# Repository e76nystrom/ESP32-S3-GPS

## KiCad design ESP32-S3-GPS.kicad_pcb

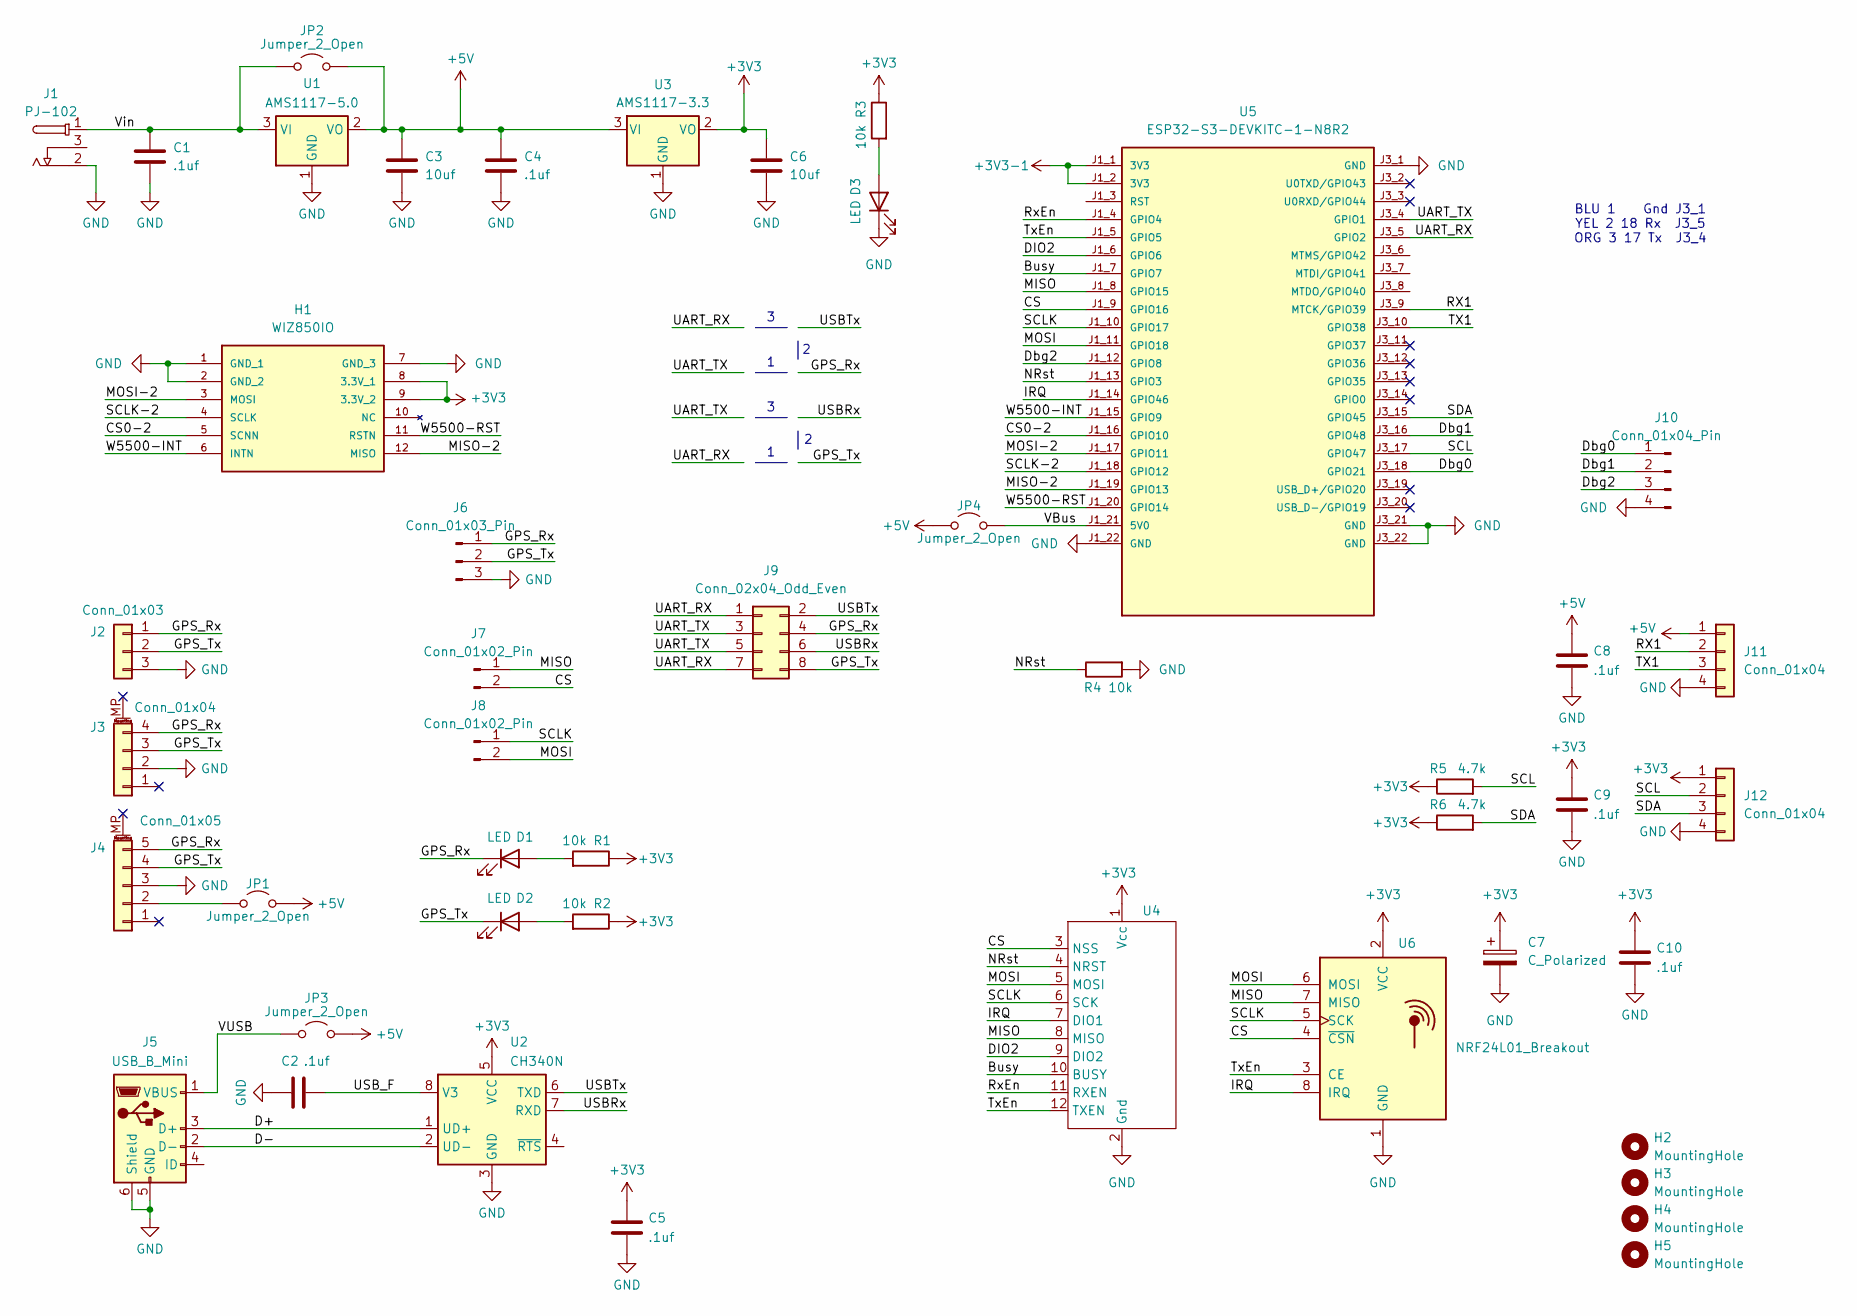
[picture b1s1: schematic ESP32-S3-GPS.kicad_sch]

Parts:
C1, C2, C4, C5, C8, C9, C10: .1uf; C_0805_2012Metric_Pad1.18x1.45mm_HandSolder
C3, C6: 10uf; C_0805_2012Metric_Pad1.18x1.45mm_HandSolder
C7: C_Polarized; CP_EIA-3528-12_Kemet-T_HandSolder
D1, D2, D3: LED; LED_0603_1608Metric_Pad1.05x1.35mm_HandSolder
H1: WIZ850IO; MANUFACTURER_PART_NUMBER WIZ850IO
H2, H3, H4, H5: MountingHole; MountingHole_1-8_1-4
J1: PJ-102; PJ-102-3.81mm
J2: Conn_01x03; JST_XH_B3B-XH-A_1x03_P2.50mm_Vertical
J3: Conn_01x04; JST_GH_SM04B-GHS-TB_1x04-1MP_P1.25mm_Horizontal
J4: Conn_01x05; JST_GH_SM05B-GHS-TB_1x05-1MP_P1.25mm_Horizontal
J5: USB_B_Mini; USB_Mini_B
J6: Conn_01x03_Pin; PinHeader_1x03_P2.54mm_Vertical
J7, J8: Conn_01x02_Pin; PinHeader_1x02_P2.54mm_Vertical
J9: Conn_02x04_Odd_Even; PinHeader_2x04_P2.54mm_Vertical
J10: Conn_01x04_Pin; PinHeader_1x04_P2.54mm_Vertical
J11, J12: Conn_01x04; JST_XH_B4B-XH-A_1x04_P2.50mm_Vertical
JP1, JP3, JP4: Jumper_2_Open; R_0805_2012Metric_Pad1.20x1.40mm_HandSolder
JP2: Jumper_2_Open; R_1206_3216Metric_Pad1.30x1.75mm_HandSolder
R1, R2, R3, R4: 10k; R_0805_2012Metric_Pad1.20x1.40mm_HandSolder
R5, R6: 4.7k; R_0805_2012Metric_Pad1.20x1.40mm_HandSolder
U1: AMS1117-5.0; SOT-223-3_TabPin2
U2: CH340N; JEITA_SOIC-8_3.9x4.9mm_P1.27mm
U3: AMS1117-3.3; SOT-223-3_TabPin2
U4: PinSocket_2x06_P2.54mm_Vertical
U5: ESP32-S3-DEVKITC-1-N8R2; ESP32-S3; PARTREV V1
U6: NRF24L01_Breakout; nRF24L01_Breakout

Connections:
+3V3: C5.1, C6.1, C7.1, C9.1, C10.1, H1.8 (3.3V_1), H1.9 (3.3V_2), J12.1, R1.1, R2.1, R3.1, R5.1, R6.1, U2.5 (VCC), U3.2 (VO), U4.1 (Vcc), U6.2 (VCC)
+3V3-1: U5.J1_1 (3V3), U5.J1_2 (3V3)
+5V: C3.1, C4.1, C8.1, J11.1, JP1.1 (A), JP2.2 (B), JP3.2 (B), JP4.2 (B), U1.2 (VO), U3.3 (VI)
/Busy: U4.10 (BUSY), U5.J1_7 (GPIO7)
/CS: J7.2, U4.3 (NSS), U5.J1_9 (GPIO16), U6.4 (~CSN)
/CS0-2: H1.5 (SCNN), U5.J1_16 (GPIO10)
/D+: J5.3 (D+), U2.1 (UD+)
/D-: J5.2 (D-), U2.2 (UD-)
/DIO2: U4.9 (DIO2), U5.J1_6 (GPIO6)
/Dbg0: J10.1, U5.J3_18 (GPIO21)
/Dbg1: J10.2, U5.J3_16 (GPIO48)
/Dbg2: J10.3, U5.J1_12 (GPIO8)
/GPS_Rx: D1.1 (K), J2.1, J3.4, J4.5, J6.1, J9.4
/GPS_Tx: D2.1 (K), J2.2, J3.3, J4.4, J6.2, J9.8
/IRQ: U4.7 (DIO1), U5.J1_14 (GPIO46), U6.8 (IRQ)
/MISO: J7.1, U4.8 (MISO), U5.J1_8 (GPIO15), U6.7 (MISO)
/MISO-2: H1.12 (MISO), U5.J1_19 (GPIO13)
/MOSI: J8.2, U4.5 (MOSI), U5.J1_11 (GPIO18), U6.6 (MOSI)
/MOSI-2: H1.3 (MOSI), U5.J1_17 (GPIO11)
/NRst: R4.1, U4.4 (NRST), U5.J1_13 (GPIO3)
/RX1: J11.2, U5.J3_9 (MTCK/GPIO39)
/RxEn: U4.11 (RXEN), U5.J1_4 (GPIO4)
/SCL: J12.2, R5.2, U5.J3_17 (GPIO47)
/SCLK: J8.1, U4.6 (SCK), U5.J1_10 (GPIO17), U6.5 (SCK)
/SCLK-2: H1.4 (SCLK), U5.J1_18 (GPIO12)
/SDA: J12.3, R6.2, U5.J3_15 (GPIO45)
/TX1: J11.3, U5.J3_10 (GPIO38)
/TxEn: U4.12 (TXEN), U5.J1_5 (GPIO5), U6.3 (CE)
/UART_RX: J9.1, J9.7, U5.J3_5 (GPIO2)
/UART_TX: J9.3, J9.5, U5.J3_4 (GPIO1)
/USBRx: J9.6, U2.7 (RXD)
/USBTx: J9.2, U2.6 (TXD)
/USB_F: C2.1, U2.8 (V3)
/VBus: JP4.1 (A), U5.J1_21 (5V0)
/VUSB: J5.1 (VBUS), JP3.1 (A)
/Vin: C1.1, J1.1, JP2.1 (A), U1.3 (VI)
/W5500-INT: H1.6 (INTN), U5.J1_15 (GPIO9)
/W5500-RST: H1.11 (RSTN), U5.J1_20 (GPIO14)
GND: C1.2, C2.2, C3.2, C4.2, C5.2, C6.2, C7.2, C8.2, C9.2, C10.2, D3.1 (K), H1.1 (GND_1), H1.2 (GND_2), H1.7 (GND_3), J1.2, J2.3, J3.2, J4.3, J5.5 (GND), J5.6 (Shield), J6.3, J10.4, J11.4, J12.4, R4.2, U1.1 (GND), U2.3 (GND), U3.1 (GND), U4.2 (Gnd), U5.J1_22 (GND), U5.J3_1 (GND), U5.J3_21 (GND), U5.J3_22 (GND), U6.1 (GND)
unnamed: D1.2 (A), R1.2
unnamed: D2.2 (A), R2.2
unnamed: D3.2 (A), R3.2
unnamed: J4.2, JP1.2 (B)

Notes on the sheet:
BLU 1 Gnd J3_1 YEL 2 18 Rx J3_5 ORG 3 17 Tx J3_4

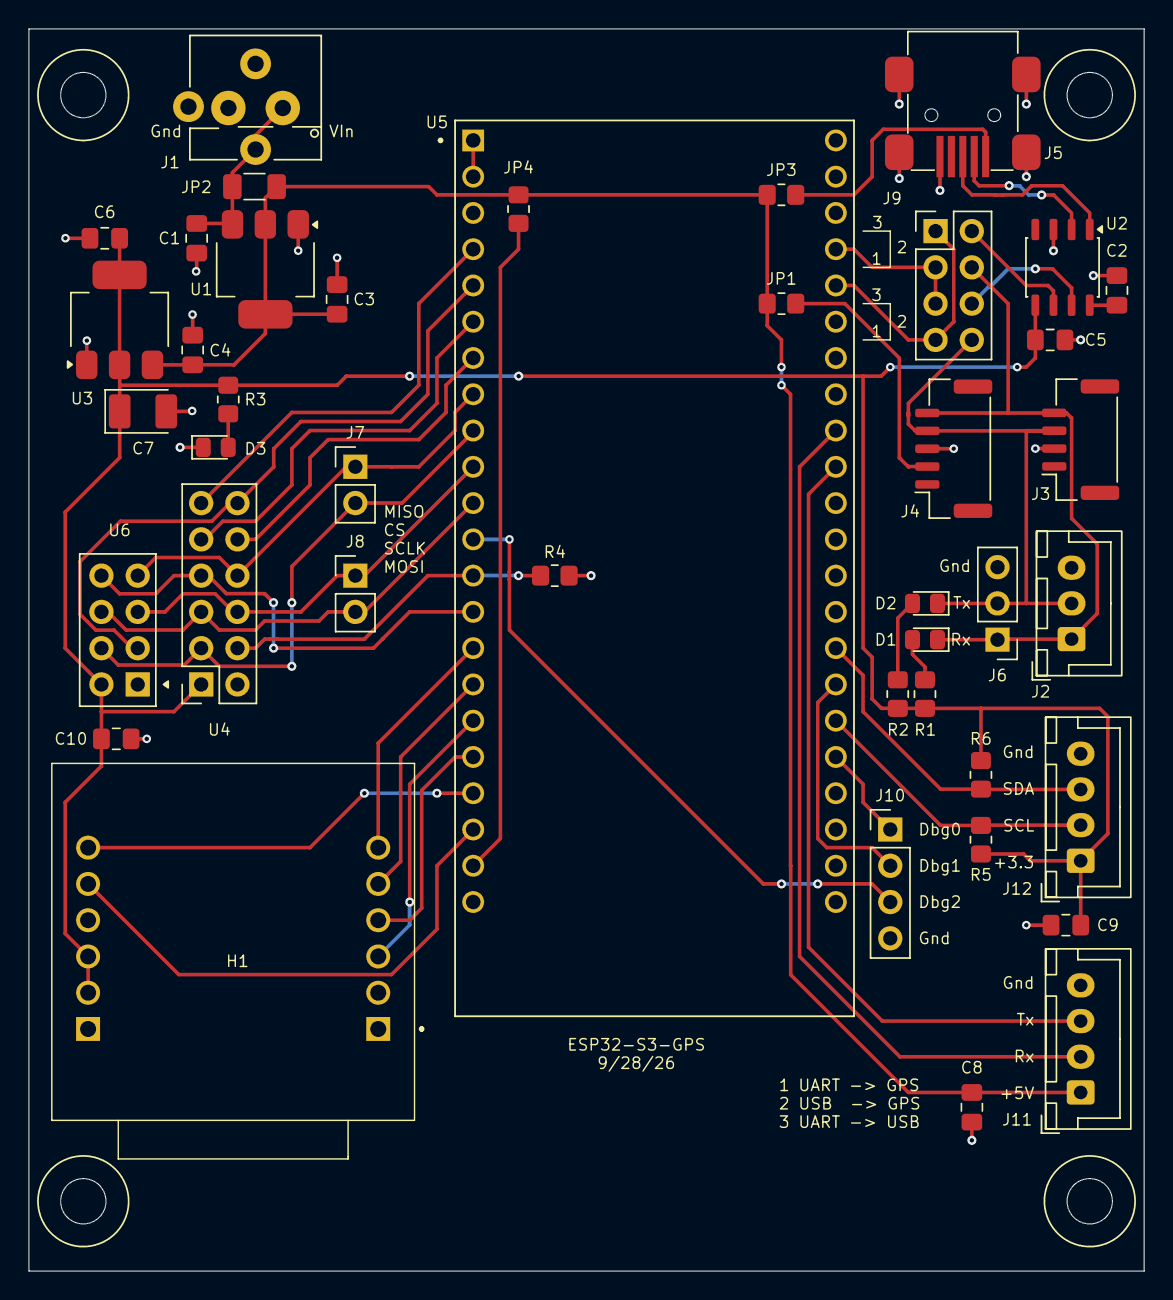
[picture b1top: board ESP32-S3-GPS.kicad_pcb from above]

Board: 2 copper layers, 78.1 x 87.0 mm, 46 parts (0 on the bottom side), 43 nets.
